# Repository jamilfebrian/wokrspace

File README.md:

# jamil-tinkpad-repository
tempat menyimpan data dari laptop tinkpad

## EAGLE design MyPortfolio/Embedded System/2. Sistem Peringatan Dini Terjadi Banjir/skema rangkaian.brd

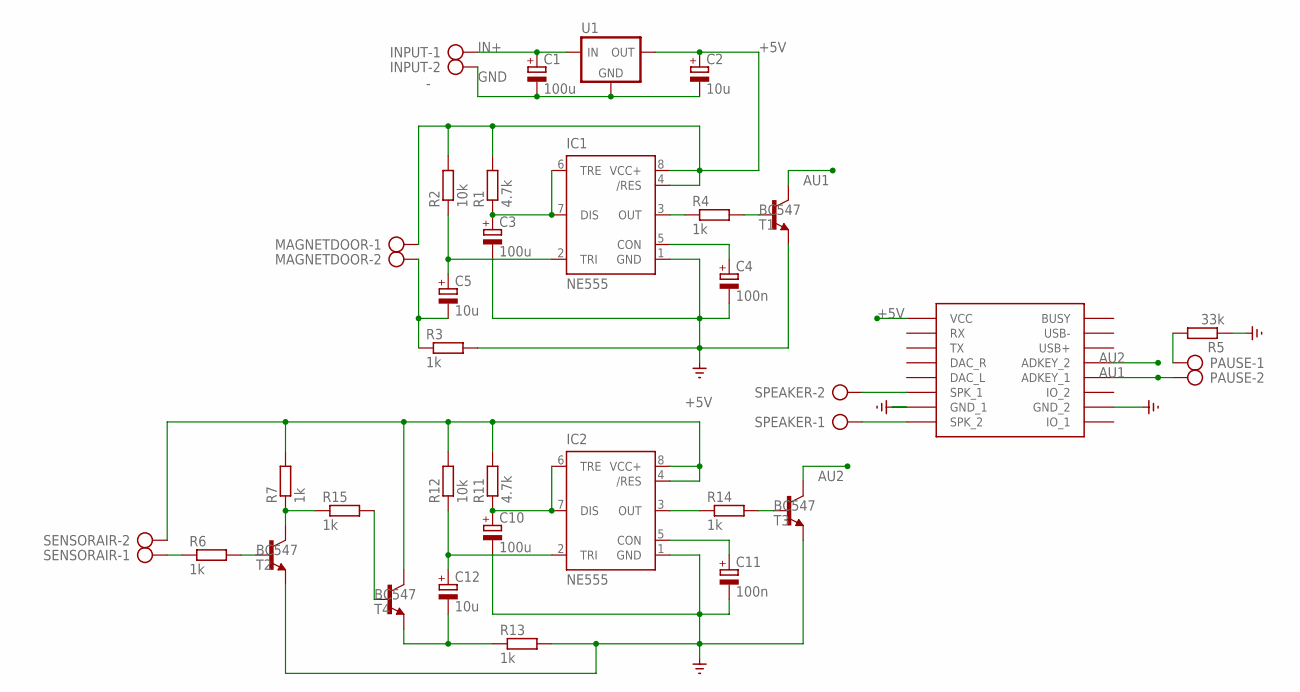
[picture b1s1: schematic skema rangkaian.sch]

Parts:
C1, C3, C10: 100u; E2-5
C2, C5, C12: 10u; E2-5
C4, C11: 100n; E2-5
IC1, IC2: NE555; DIL-08
INPUT: -; AK500/2-H
MAGNETDOOR: AK500/2-H
PAUSE: AK500/2-H
R1, R11: 4.7k; 0207/10
R2, R12: 10k; 0207/10
R3, R4, R6, R7, R13, R14, R15: 1k; 0207/10
R5: 33k; 0207/10
SENSORAIR: AK500/2-H
SPEAKER: AK500/2-H
T1, T2, T3, T4: BC547; TO92
U1: 78XX-TO220V; TO220BV
U$1: DFPLAYER

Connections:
+5V: C2.+, IC1.4 (/RES), IC1.8 (VCC+), IC2.4 (/RES), IC2.8 (VCC+), MAGNETDOOR.1, R1.2, R2.2, R7.2, R11.2, R12.2, SENSORAIR.2, T4.3 (C), U1.3 (VOUT), U$1.VCC
AU1: PAUSE.2, T1.3 (C), U$1.ADKEY1 (ADKEY_1)
AU2: T3.3 (C), U$1.ADKEY2 (ADKEY_2)
GND: C1.-, C2.-, C3.-, C4.-, C10.-, C11.-, IC1.1 (GND), IC2.1 (GND), INPUT.2, R3.2, R5.1, R13.2, T1.1 (E), T2.1 (E), T3.1 (E), U1.2 (GND), U$1.GND_1, U$1.GND_2
IN+: C1.+, INPUT.1, U1.1 (VIN)
unnamed: R14.2, T3.2 (B)
unnamed: R6.2, T2.2 (B)
unnamed: C3.+, IC1.6 (TRE), IC1.7 (DIS), R1.1
unnamed: C10.+, IC2.6 (TRE), IC2.7 (DIS), R11.1
unnamed: C4.+, IC1.5 (CON)
unnamed: C5.+, IC1.2 (TRI), R2.1
unnamed: C5.-, MAGNETDOOR.2, R3.1
unnamed: IC1.3 (OUT), R4.1
unnamed: R4.2, T1.2 (B)
unnamed: PAUSE.1, R5.2
unnamed: C11.+, IC2.5 (CON)
unnamed: C12.+, IC2.2 (TRI), R12.1
unnamed: C12.-, R13.1, T4.1 (E)
unnamed: IC2.3 (OUT), R14.1
unnamed: SPEAKER.2, U$1.SPK1 (SPK_1)
unnamed: R6.1, SENSORAIR.1
unnamed: R7.1, R15.1, T2.3 (C)
unnamed: R15.2, T4.2 (B)
unnamed: SPEAKER.1, U$1.SPK2 (SPK_2)

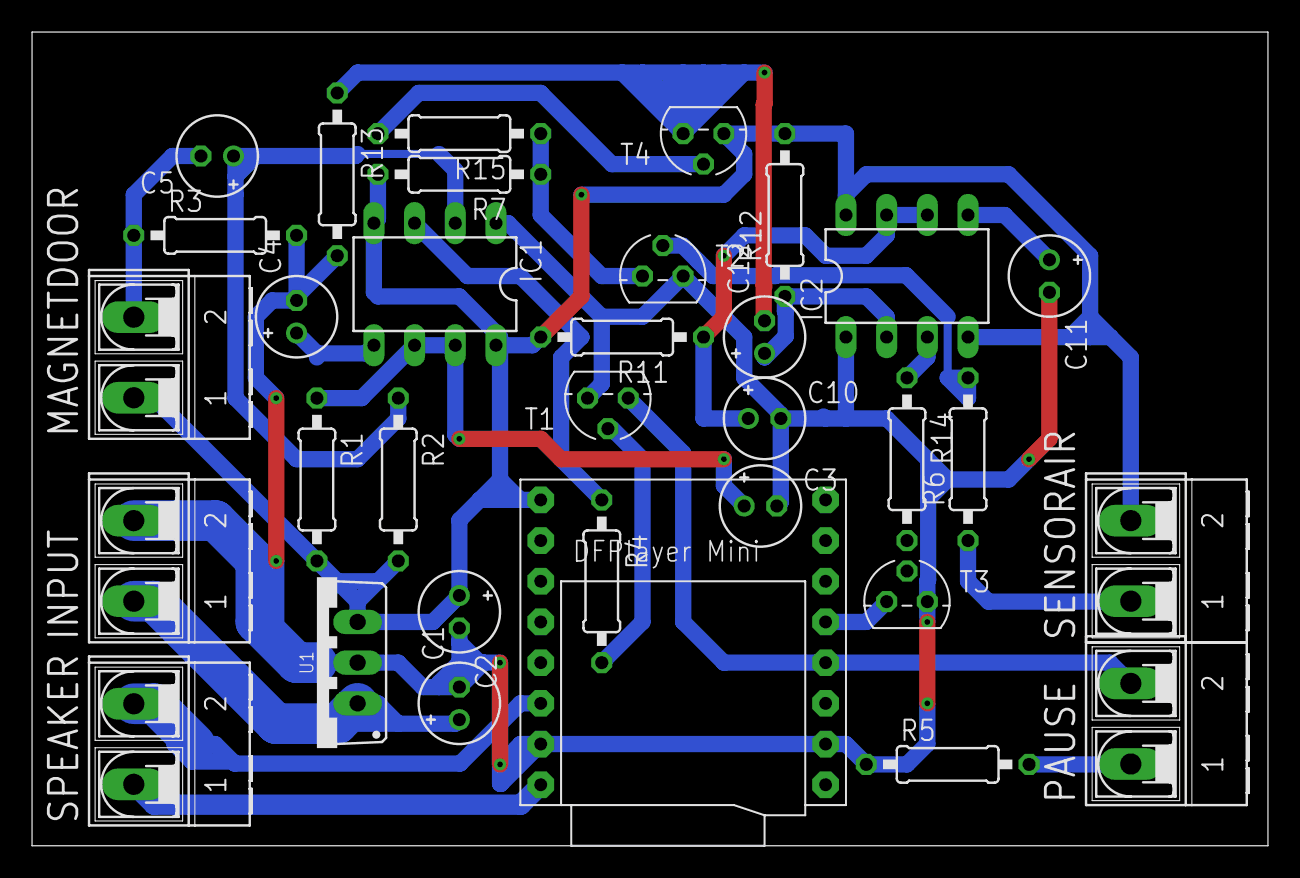
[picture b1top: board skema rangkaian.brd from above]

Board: 2 copper layers, 77.1 x 50.8 mm, 33 parts (0 on the bottom side), 24 nets.

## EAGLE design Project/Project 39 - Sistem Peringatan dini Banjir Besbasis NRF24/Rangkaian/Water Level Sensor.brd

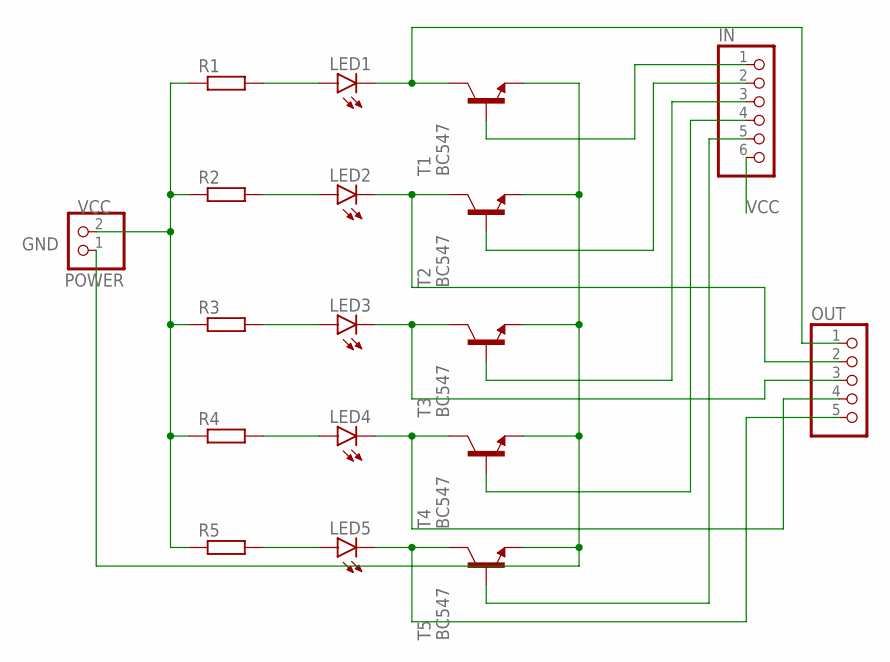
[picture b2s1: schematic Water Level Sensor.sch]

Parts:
IN: PINHD-1X6; 1X06
LED1, LED2, LED3, LED4, LED5: LED5MM
OUT: PINHD-1X5; 1X05
POWER: PINHD-1X2; 1X02
R1, R2, R3, R4, R5: R-EU_0204/7; 0204/7
T1, T2, T3, T4, T5: BC547; TO92

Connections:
GND: POWER.1, T1.1 (E), T2.1 (E), T3.1 (E), T4.1 (E), T5.1 (E)
unnamed: LED1.K (C), OUT.1, T1.3 (C)
unnamed: LED2.K (C), OUT.2, T2.3 (C)
unnamed: LED3.K (C), OUT.3, T3.3 (C)
unnamed: LED4.K (C), OUT.4, T4.3 (C)
unnamed: LED1.A, R1.2
unnamed: LED2.A, R2.2
unnamed: LED3.A, R3.2
unnamed: LED4.A, R4.2
unnamed: LED5.A, R5.2
unnamed: IN.1, T1.2 (B)
unnamed: IN.2, T2.2 (B)
unnamed: IN.3, T3.2 (B)
unnamed: IN.4, T4.2 (B)
unnamed: IN.5, T5.2 (B)
unnamed: LED5.K (C), OUT.5, T5.3 (C)
VCC: IN.6, POWER.2, R1.1, R2.1, R3.1, R4.1, R5.1

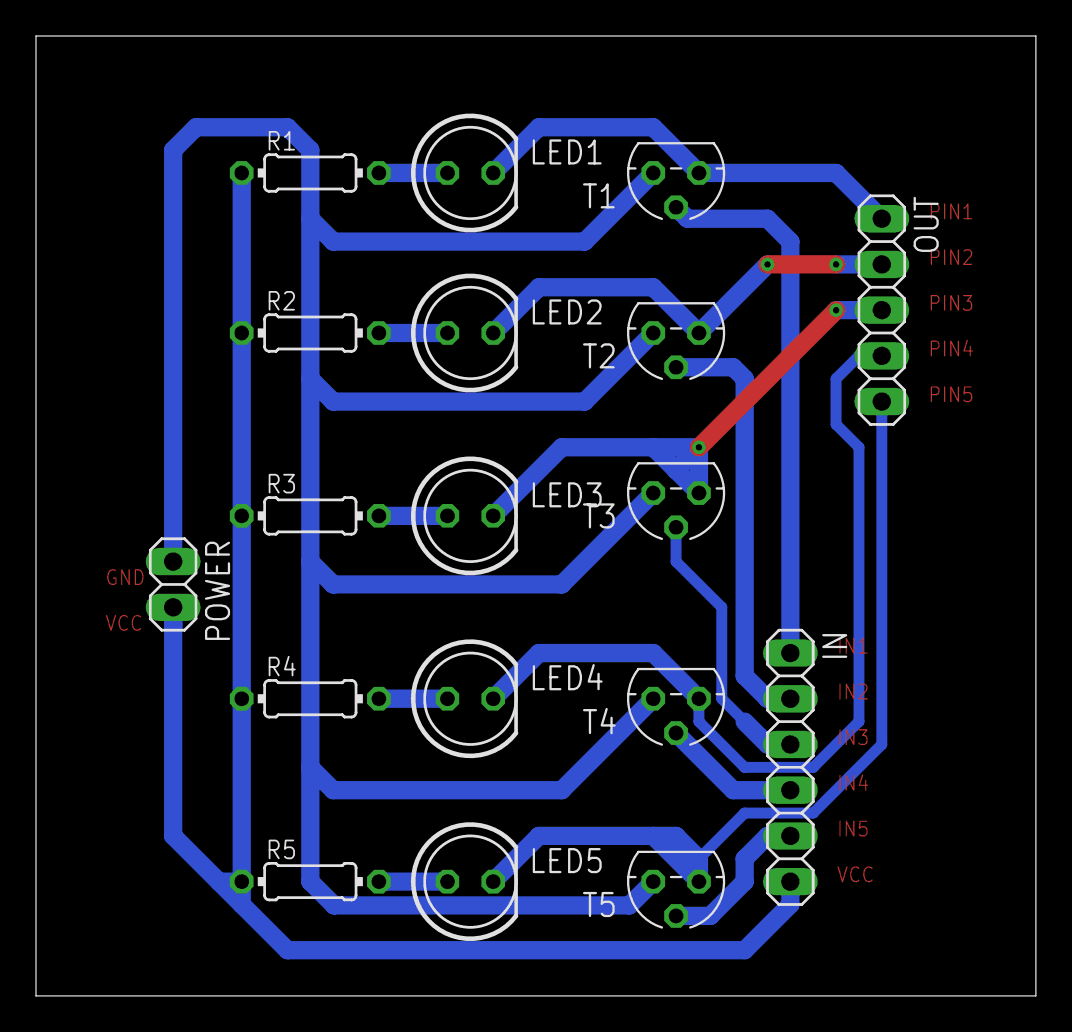
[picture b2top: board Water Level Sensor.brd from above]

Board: 2 copper layers, 55.5 x 53.3 mm, 18 parts (0 on the bottom side), 17 nets.

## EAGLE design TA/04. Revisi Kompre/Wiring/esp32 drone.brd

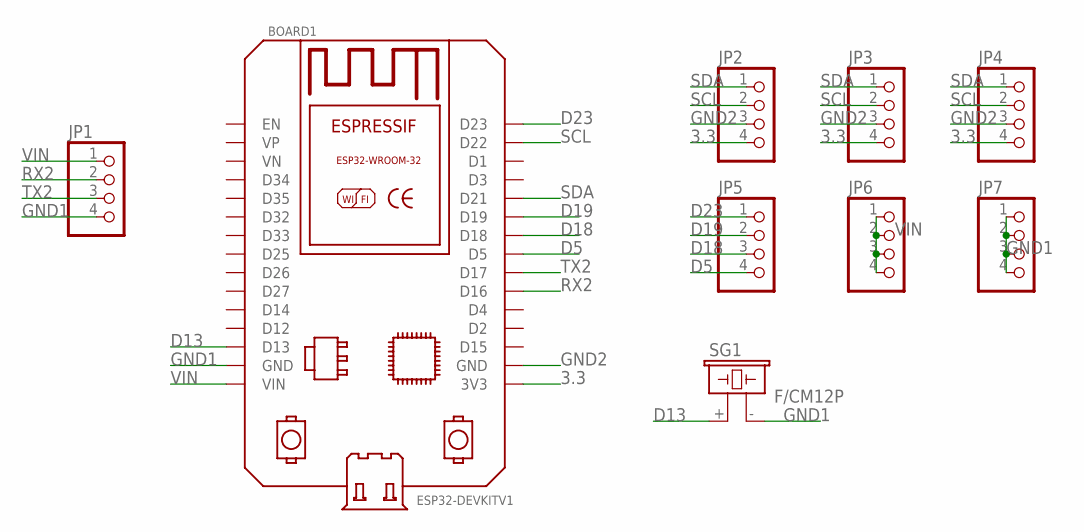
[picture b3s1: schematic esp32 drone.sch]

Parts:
BOARD1: ESP32DEVKITV1; ESP32-DEVKITV1
JP1, JP2, JP3, JP4, JP5, JP6, JP7: PINHD-1X4; 1X04
SG1: F/CM12P

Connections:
3.3: BOARD1.3V3, JP2.4, JP3.4, JP4.4
D5: BOARD1.D5, JP5.4
D13: BOARD1.D13, SG1.+ (1)
D18: BOARD1.D18, JP5.3
D19: BOARD1.D19, JP5.2
D23: BOARD1.D23, JP5.1
GND1: BOARD1.GND, JP1.4, JP7.1, JP7.2, JP7.3, JP7.4, SG1.- (2)
GND2: BOARD1.GND@1 (GND), JP2.3, JP3.3, JP4.3
RX2: BOARD1.D16, JP1.2
SCL: BOARD1.D22, JP2.2, JP3.2, JP4.2
SDA: BOARD1.D21, JP2.1, JP3.1, JP4.1
TX2: BOARD1.D17, JP1.3
VIN: BOARD1.VIN, JP1.1, JP6.1, JP6.2, JP6.3, JP6.4

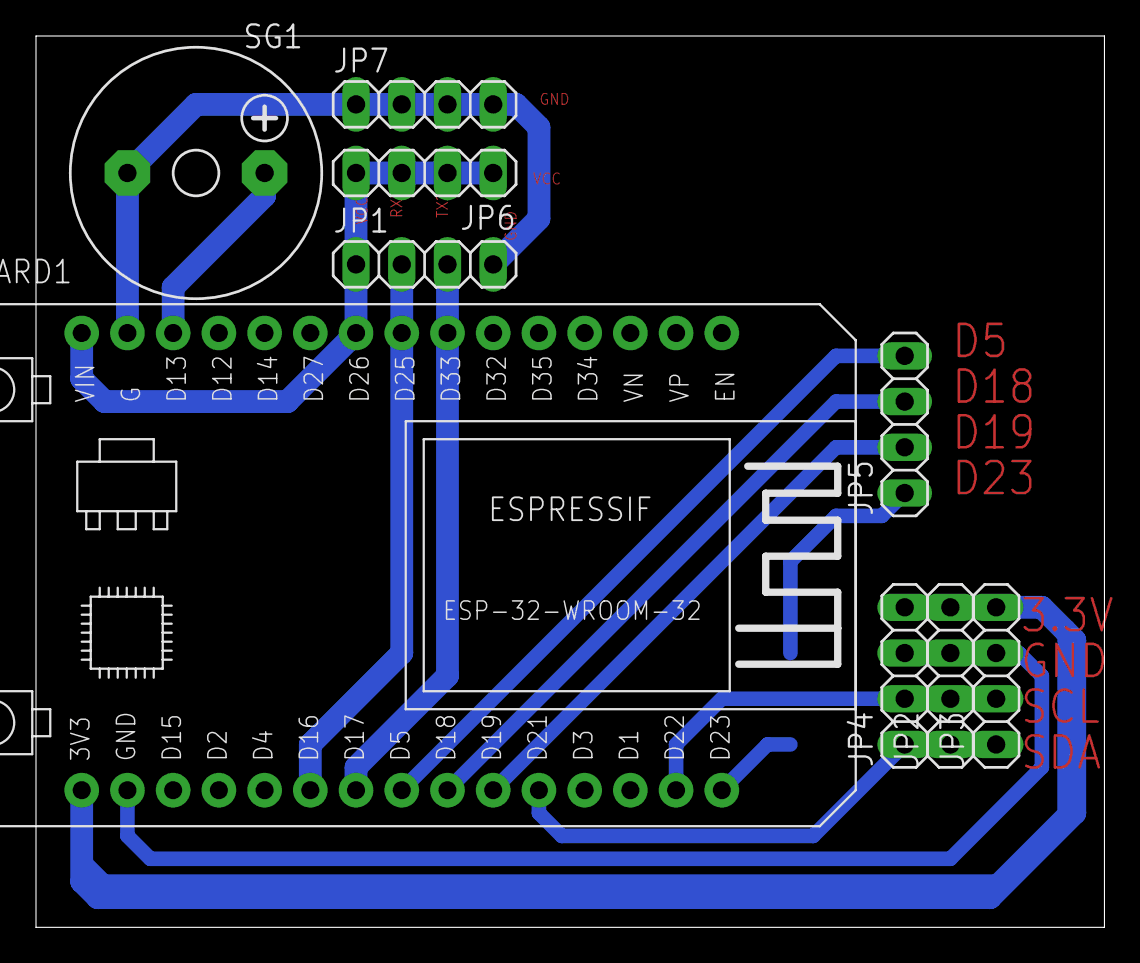
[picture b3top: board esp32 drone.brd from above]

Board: 2 copper layers, 59.4 x 49.5 mm, 9 parts (0 on the bottom side), 13 nets.

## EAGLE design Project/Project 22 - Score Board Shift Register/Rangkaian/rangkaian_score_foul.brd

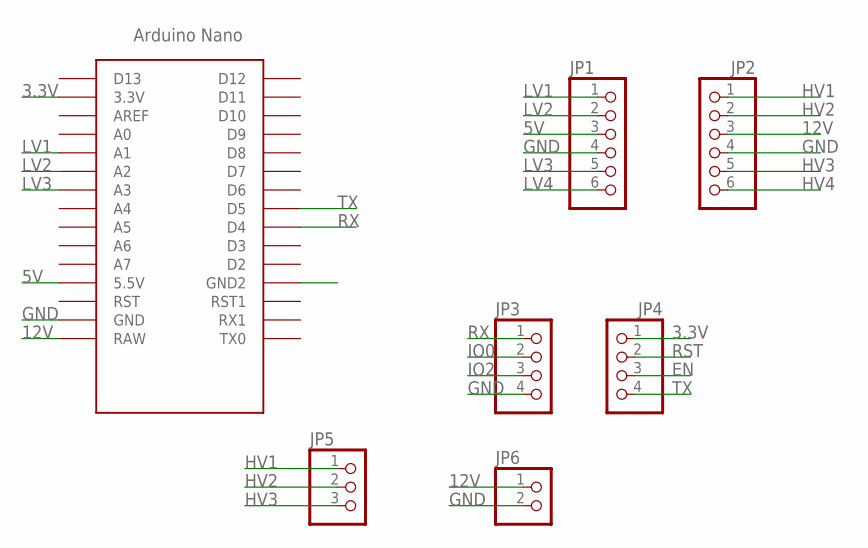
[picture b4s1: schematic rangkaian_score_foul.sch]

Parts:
JP1, JP2: PINHD-1X6; 1X06
JP3, JP4: PINHD-1X4; 1X04
JP5: PINHD-1X3; 1X03
JP6: PINHD-1X2; 1X02
U$1: NANO

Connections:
3.3V: JP4.1, U$1.3.3V
5V: JP1.3, U$1.5V (5.5V)
12V: JP2.3, JP6.1, U$1.RAW
EN: JP4.3
GND: JP1.4, JP2.4, JP3.4, JP6.2, U$1.GND
HV1: JP2.1, JP5.1
HV2: JP2.2, JP5.2
HV3: JP2.5, JP5.3
HV4: JP2.6
IO0: JP3.2
IO2: JP3.3
LV1: JP1.1, U$1.A1
LV2: JP1.2, U$1.A2
LV3: JP1.5, U$1.A3
LV4: JP1.6
RST: JP4.2
RX: JP3.1, U$1.D4
TX: JP4.4, U$1.D5

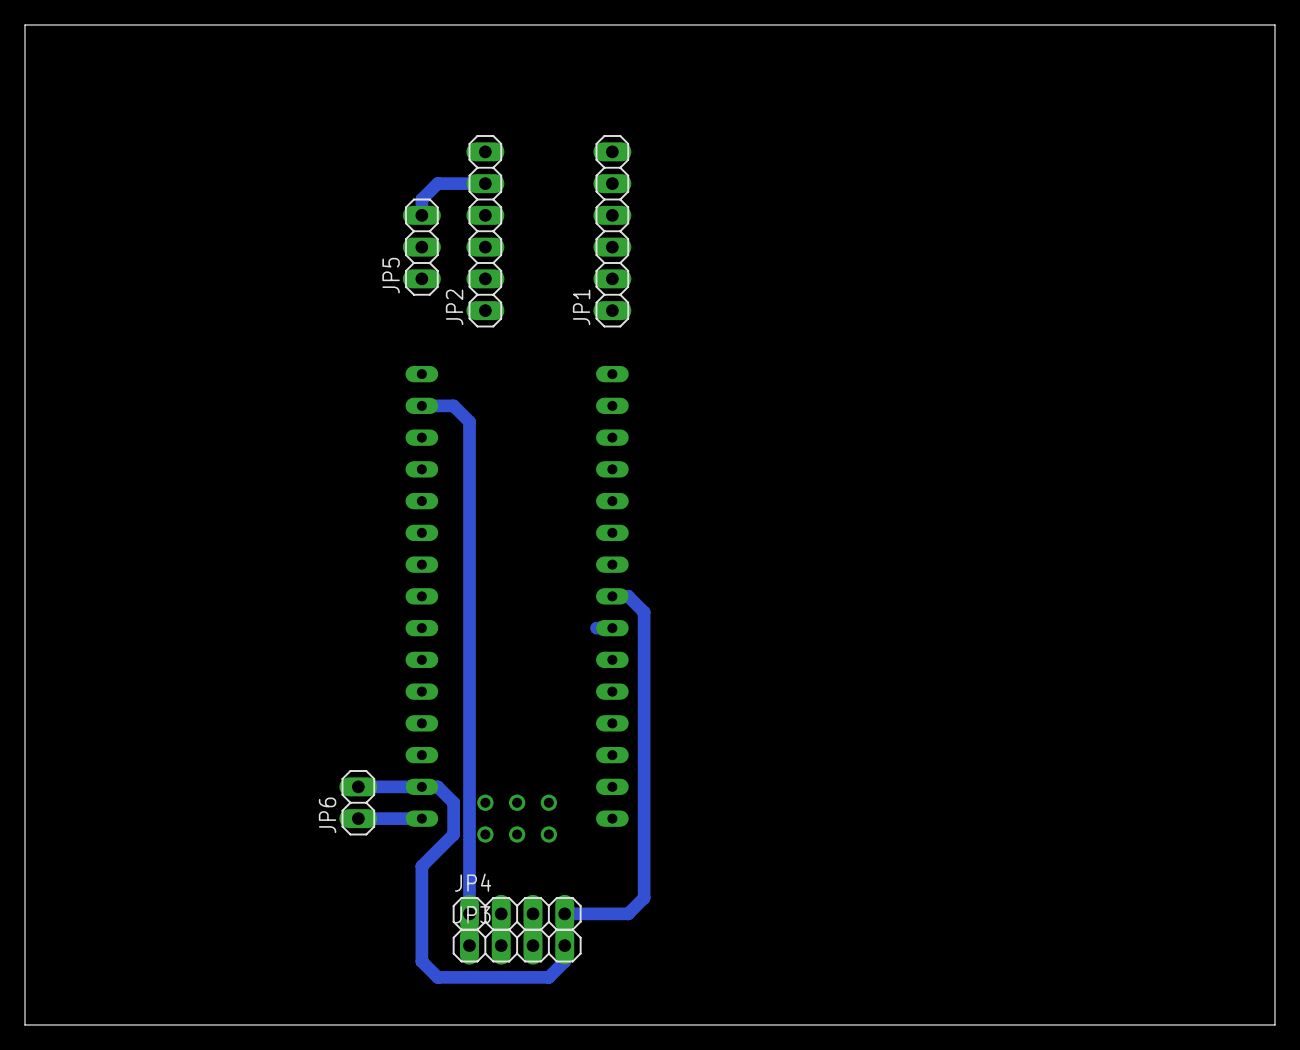
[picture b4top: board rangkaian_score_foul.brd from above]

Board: 2 copper layers, 100.0 x 80.0 mm, 7 parts (0 on the bottom side), 12 nets.

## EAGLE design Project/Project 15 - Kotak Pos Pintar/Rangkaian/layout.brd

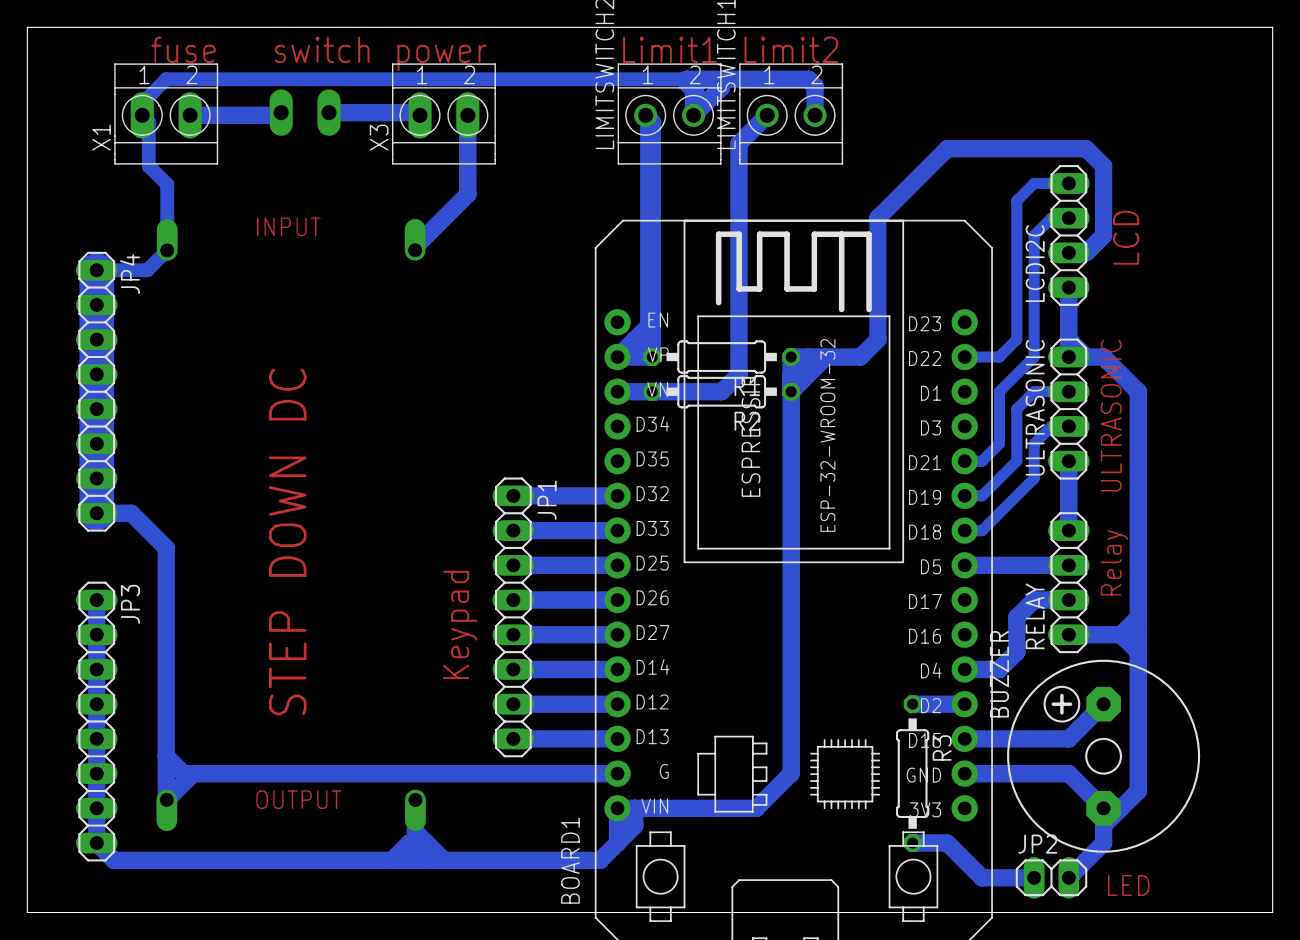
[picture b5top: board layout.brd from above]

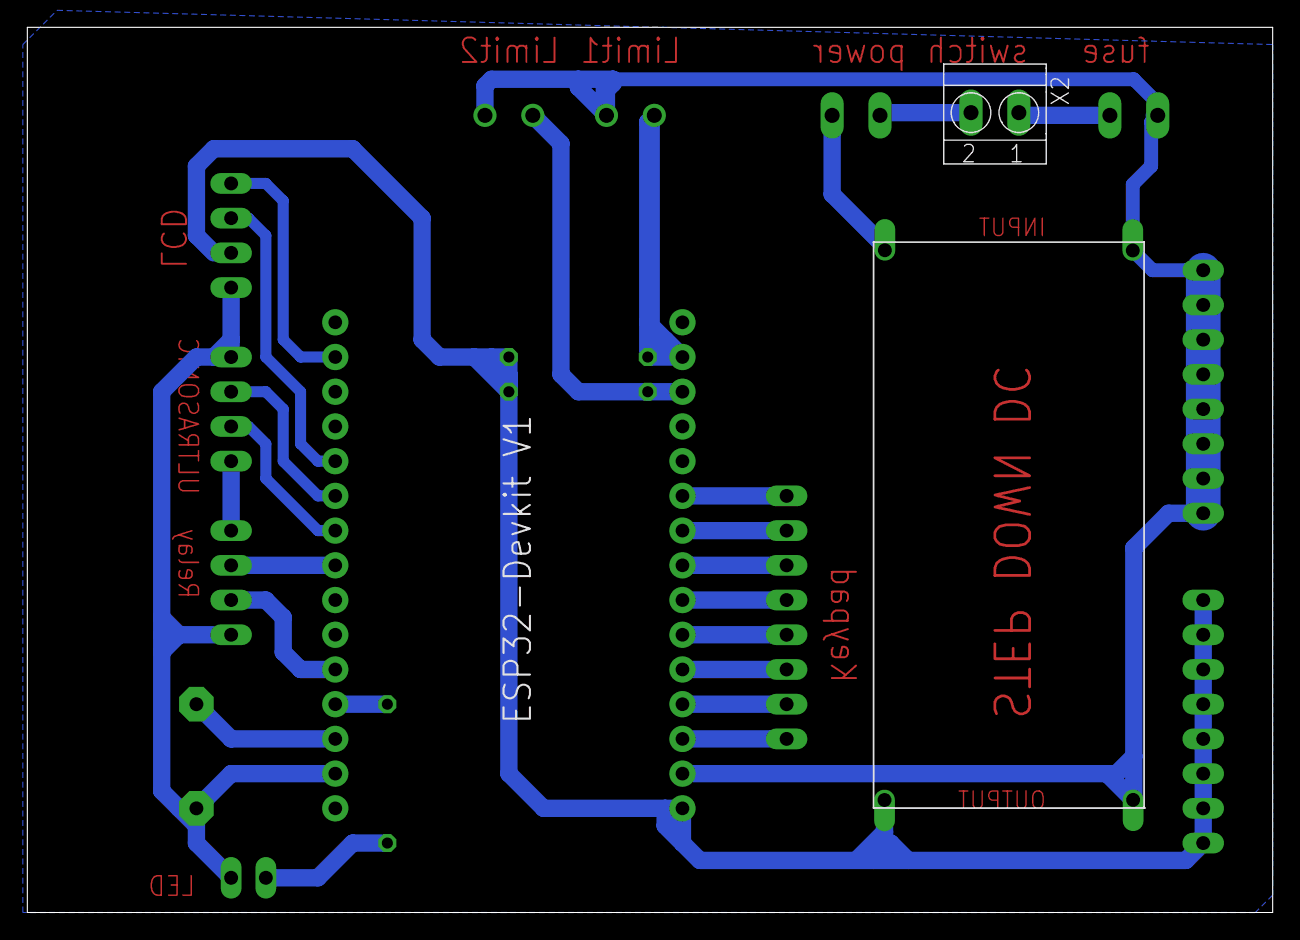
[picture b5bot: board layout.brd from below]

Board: 2 copper layers, 91.1 x 64.8 mm, 18 parts (2 on the bottom side), 25 nets.

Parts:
BOARD1: ESP32DEVKITV1SHRIDATTDUDHAT; ESP32-DEVKITV1
BUZZER: F/CM12P
JP1, JP3, JP4: 1X08
JP2: 1X02
LCDI2C: 1X04
LIMITSWITCH1, LIMITSWITCH2: TERMINAL-BLOCK-3.5MM-2-PIN-ROUND-PAD; TERMINAL-BLOCK-2-PIN-3.5MM-ROUND-PAD
R1, R2, R3: 0207/10
RELAY: 1X04
STEP_DOWN1: LM2596HVS
ULTRASONIC: 1X04
X1, X2, X3: TERMINAL-BLOCK-3.5MM-2-PIN-LONG-PAD; TERMINAL-BLOCK-2-PIN-3.5MM-LONG-PAD

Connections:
5V: BOARD1.VIN, JP3.1, JP3.2, JP3.3, JP3.4, JP3.5, JP3.6, JP3.7, JP3.8, LCDI2C.2, R1.1, R2.1, RELAY.4, STEP_DOWN1.OUT+, ULTRASONIC.1
BUZZ: BOARD1.D15, BUZZER.+
ECHO: BOARD1.D19, ULTRASONIC.3
GND: BOARD1.GND@1, BUZZER.-, JP2.2, LCDI2C.1, RELAY.1, ULTRASONIC.4
GND1: BOARD1.GND, JP4.1, JP4.2, JP4.3, JP4.4, JP4.5, JP4.6, JP4.7, JP4.8, LIMITSWITCH1.2, LIMITSWITCH2.2, STEP_DOWN1.IN-, STEP_DOWN1.OUT-, X1.1
IN1: BOARD1.D4, RELAY.2
IN2: BOARD1.D5, RELAY.3
IN+: STEP_DOWN1.IN+, X3.2
LED: BOARD1.D2, R3.1
LIMITSW1: BOARD1.VP, LIMITSWITCH2.1, R1.2
LIMITSW2: BOARD1.VN, LIMITSWITCH1.1, R2.2
unnamed: JP2.1, R3.2
unnamed: X1.2, X2.1
unnamed: X2.2, X3.1
unnamed: BOARD1.D13, JP1.8
unnamed: BOARD1.D12, JP1.7
unnamed: BOARD1.D14, JP1.6
unnamed: BOARD1.D27, JP1.5
unnamed: BOARD1.D26, JP1.4
unnamed: BOARD1.D25, JP1.3
unnamed: BOARD1.D33, JP1.2
unnamed: BOARD1.D32, JP1.1
SCL: BOARD1.D22, LCDI2C.4
SDA: BOARD1.D21, LCDI2C.3
TRIG: BOARD1.D18, ULTRASONIC.2

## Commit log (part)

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2024-03-11 membuat latihan taiwindcss
2024-03-11 update 11 maret 2024
2024-04-03 update 3 april 2024
2024-04-12 13 april 2024
2024-04-14 14 april 2024
2024-04-16 update 16 april 2024
2024-04-19 update project 19 april 2024
2024-04-23 23 april 2024
2024-05-08 update 8 mei 2024
2024-06-02 update 1 juni 2024
2024-06-15 update 15 juni 2024
2024-06-18 update 18 juni 2024
2024-06-29 update 29 juni 2024
2024-07-04 update 4 juli 2024
2024-07-17 update 17 juli 2024
2024-07-22 update 22 juli 2024
2024-07-28 update 28 juli 2024
2024-08-03 update 3 agustus 2024
2024-08-21 update 22 agustus 2024
2024-08-23 update 23 agustus 2024
2024-09-10 baru
2024-09-27 terbaru
2024-11-10 update 10 nov 2024
2024-12-09 update 10 12 2024
2024-12-31 update awal tahun
2025-01-02 3 jan 2025
2025-01-06 update doc 6 jan 2025
2025-01-08 dart-flutter
2025-01-17 17 january 2025
2025-02-11 update 11 Februari 2025
2025-05-27 update 27 mai 2025
2025-08-12 update 12 agustus 2025
2025-11-25 25 november 2025
2026-01-08 update 2026
2026-01-08 2026
2026-02-28 up date mak
2026-02-28 update web porto
2026-04-13 update 13 april
